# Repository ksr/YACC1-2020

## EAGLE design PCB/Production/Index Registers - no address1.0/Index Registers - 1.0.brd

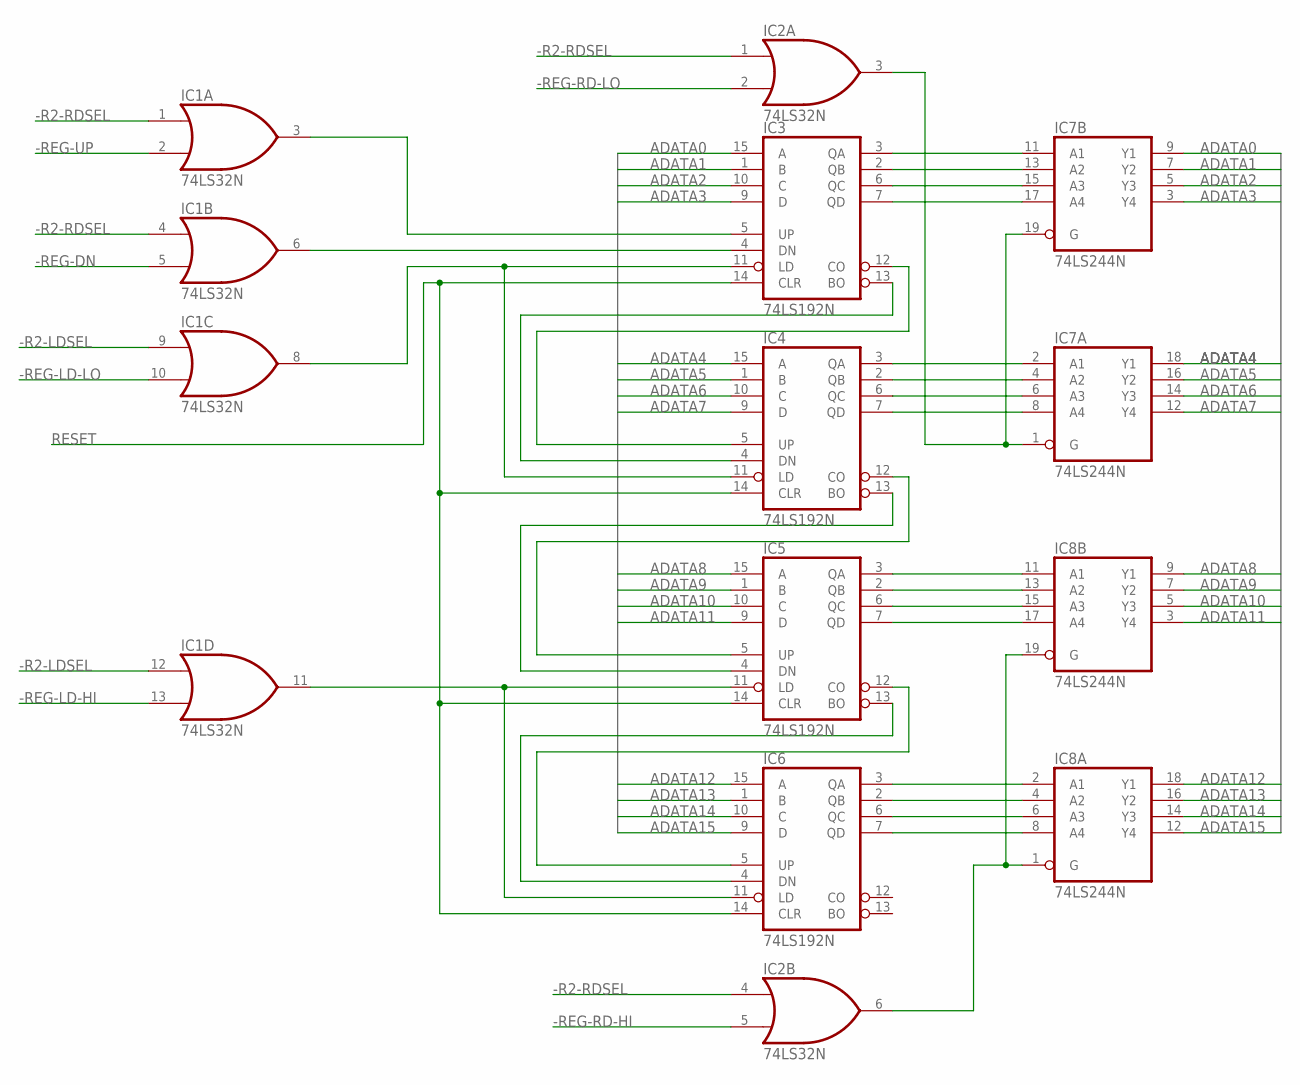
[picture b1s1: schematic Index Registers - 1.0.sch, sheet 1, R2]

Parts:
IC1, IC2: 74LS32N; DIL14
IC3, IC4, IC5, IC6: 74LS192N; DIL16
IC7, IC8: 74LS244N; DIL20

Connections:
-R2-LDSEL: IC1.9 (I0), IC1.12 (I0); also elsewhere on the board
-R2-RDSEL: IC1.1 (I0), IC1.4 (I0), IC2.1 (I0), IC2.4 (I0); also elsewhere on the board
-REG-DN: IC1.5 (I1); also elsewhere on the board
-REG-LD-HI: IC1.13 (I1); also elsewhere on the board
-REG-LD-LO: IC1.10 (I1); also elsewhere on the board
-REG-RD-HI: IC2.5 (I1); also elsewhere on the board
-REG-RD-LO: IC2.2 (I1); also elsewhere on the board
-REG-UP: IC1.2 (I1); also elsewhere on the board
ADATA0: IC3.15 (A), IC7.9 (Y1); also elsewhere on the board
ADATA1: IC3.1 (B), IC7.7 (Y2); also elsewhere on the board
ADATA2: IC3.10 (C), IC7.5 (Y3); also elsewhere on the board
ADATA3: IC3.9 (D), IC7.3 (Y4); also elsewhere on the board
ADATA4: IC4.15 (A), IC7.18 (Y1); also elsewhere on the board
ADATA5: IC4.1 (B), IC7.16 (Y2); also elsewhere on the board
ADATA6: IC4.10 (C), IC7.14 (Y3); also elsewhere on the board
ADATA7: IC4.9 (D), IC7.12 (Y4); also elsewhere on the board
ADATA8: IC5.15 (A), IC8.9 (Y1); also elsewhere on the board
ADATA9: IC5.1 (B), IC8.7 (Y2); also elsewhere on the board
ADATA10: IC5.10 (C), IC8.5 (Y3); also elsewhere on the board
ADATA11: IC5.9 (D), IC8.3 (Y4); also elsewhere on the board
ADATA12: IC6.15 (A), IC8.18 (Y1); also elsewhere on the board
ADATA13: IC6.1 (B), IC8.16 (Y2); also elsewhere on the board
ADATA14: IC6.10 (C), IC8.14 (Y3); also elsewhere on the board
ADATA15: IC6.9 (D), IC8.12 (Y4); also elsewhere on the board
GND: IC1.7 (GND), IC2.7 (GND), IC3.8 (GND), IC4.8 (GND), IC5.8 (GND), IC6.8 (GND), IC7.10 (GND), IC8.10 (GND); also elsewhere on the board
unnamed: IC3.13 (BO), IC4.4 (DN)
unnamed: IC3.12 (CO), IC4.5 (UP)
unnamed: IC4.13 (BO), IC5.4 (DN)
unnamed: IC4.12 (CO), IC5.5 (UP)
unnamed: IC5.13 (BO), IC6.4 (DN)
unnamed: IC5.12 (CO), IC6.5 (UP)
unnamed: IC1.8 (O), IC3.11 (LD), IC4.11 (LD)
unnamed: IC1.3 (O), IC3.5 (UP)
unnamed: IC1.6 (O), IC3.4 (DN)
unnamed: IC2.3 (O), IC7.1 (G), IC7.19 (G)
unnamed: IC2.6 (O), IC8.1 (G), IC8.19 (G)
unnamed: IC1.11 (O), IC5.11 (LD), IC6.11 (LD)
unnamed: IC3.3 (QA), IC7.11 (A1)
unnamed: IC3.2 (QB), IC7.13 (A2)
unnamed: IC3.6 (QC), IC7.15 (A3)
unnamed: IC3.7 (QD), IC7.17 (A4)
unnamed: IC4.3 (QA), IC7.2 (A1)
unnamed: IC4.2 (QB), IC7.4 (A2)
unnamed: IC4.6 (QC), IC7.6 (A3)
unnamed: IC4.7 (QD), IC7.8 (A4)
unnamed: IC5.3 (QA), IC8.11 (A1)
unnamed: IC5.2 (QB), IC8.13 (A2)
unnamed: IC5.6 (QC), IC8.15 (A3)
unnamed: IC5.7 (QD), IC8.17 (A4)
unnamed: IC6.3 (QA), IC8.2 (A1)
unnamed: IC6.2 (QB), IC8.4 (A2)
unnamed: IC6.6 (QC), IC8.6 (A3)
unnamed: IC6.7 (QD), IC8.8 (A4)
RESET: IC3.14 (CLR), IC4.14 (CLR), IC5.14 (CLR), IC6.14 (CLR); also elsewhere on the board
VCC: IC1.14 (VCC), IC2.14 (VCC), IC3.16 (VCC), IC4.16 (VCC), IC5.16 (VCC), IC6.16 (VCC), IC7.20 (VCC), IC8.20 (VCC); also elsewhere on the board

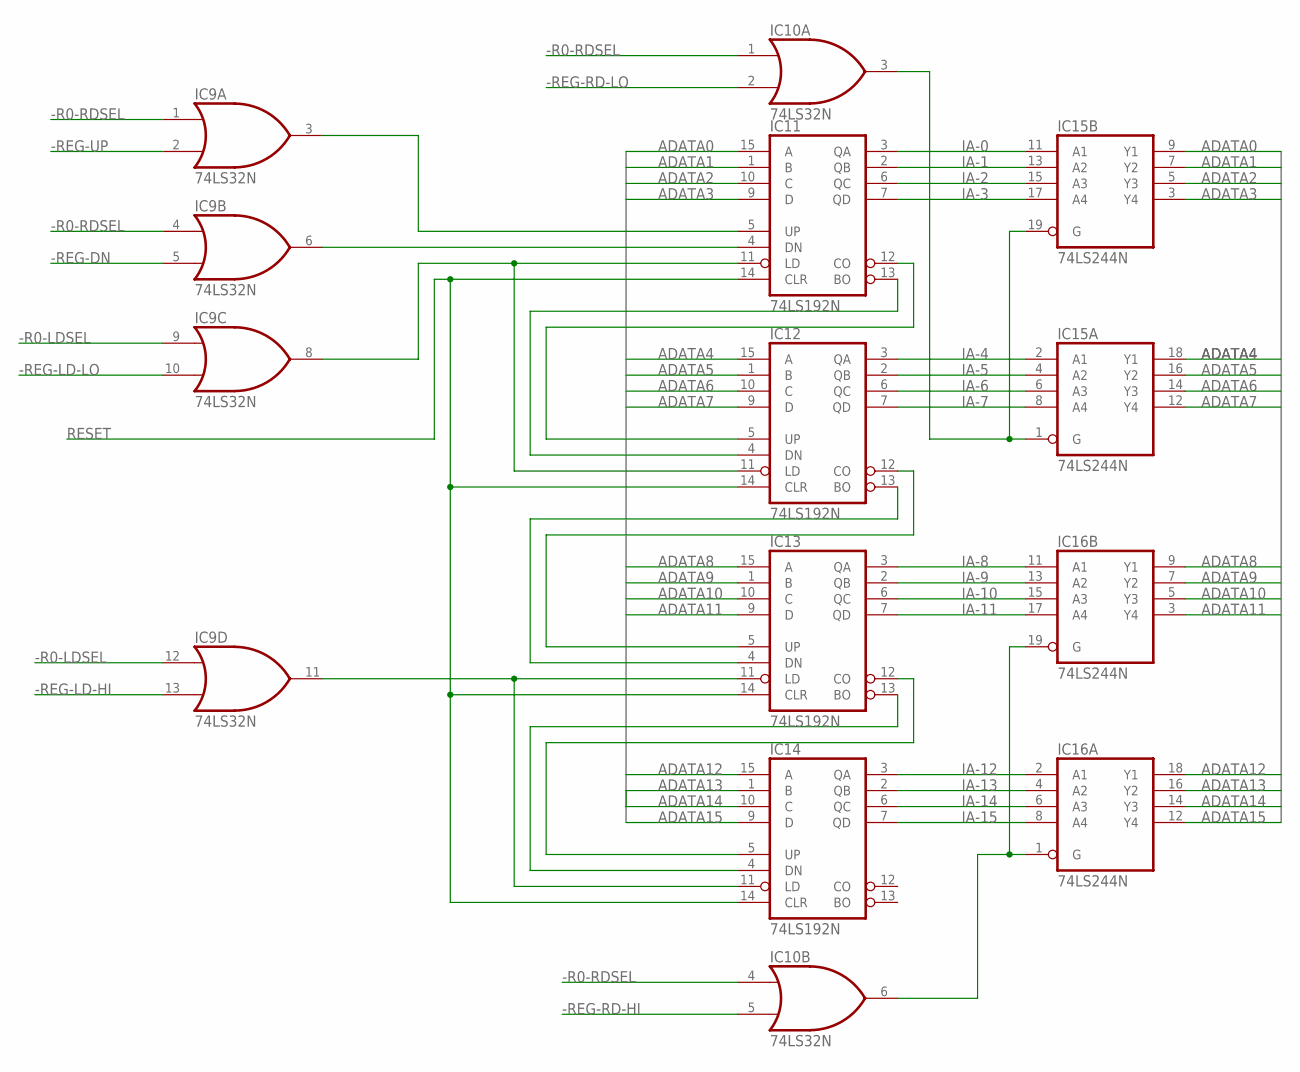
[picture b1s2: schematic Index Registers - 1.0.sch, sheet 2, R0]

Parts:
IC9, IC10: 74LS32N; DIL14
IC11, IC12, IC13, IC14: 74LS192N; DIL16
IC15, IC16: 74LS244N; DIL20

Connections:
-R0-LDSEL: IC9.9 (I0), IC9.12 (I0); also elsewhere on the board
-R0-RDSEL: IC9.1 (I0), IC9.4 (I0), IC10.1 (I0), IC10.4 (I0); also elsewhere on the board
-REG-DN: IC9.5 (I1); also elsewhere on the board
-REG-LD-HI: IC9.13 (I1); also elsewhere on the board
-REG-LD-LO: IC9.10 (I1); also elsewhere on the board
-REG-RD-HI: IC10.5 (I1); also elsewhere on the board
-REG-RD-LO: IC10.2 (I1); also elsewhere on the board
-REG-UP: IC9.2 (I1); also elsewhere on the board
ADATA0: IC11.15 (A), IC15.9 (Y1); also elsewhere on the board
ADATA1: IC11.1 (B), IC15.7 (Y2); also elsewhere on the board
ADATA2: IC11.10 (C), IC15.5 (Y3); also elsewhere on the board
ADATA3: IC11.9 (D), IC15.3 (Y4); also elsewhere on the board
ADATA4: IC12.15 (A), IC15.18 (Y1); also elsewhere on the board
ADATA5: IC12.1 (B), IC15.16 (Y2); also elsewhere on the board
ADATA6: IC12.10 (C), IC15.14 (Y3); also elsewhere on the board
ADATA7: IC12.9 (D), IC15.12 (Y4); also elsewhere on the board
ADATA8: IC13.15 (A), IC16.9 (Y1); also elsewhere on the board
ADATA9: IC13.1 (B), IC16.7 (Y2); also elsewhere on the board
ADATA10: IC13.10 (C), IC16.5 (Y3); also elsewhere on the board
ADATA11: IC13.9 (D), IC16.3 (Y4); also elsewhere on the board
ADATA12: IC14.15 (A), IC16.18 (Y1); also elsewhere on the board
ADATA13: IC14.1 (B), IC16.16 (Y2); also elsewhere on the board
ADATA14: IC14.10 (C), IC16.14 (Y3); also elsewhere on the board
ADATA15: IC14.9 (D), IC16.12 (Y4); also elsewhere on the board
GND: IC9.7 (GND), IC10.7 (GND), IC11.8 (GND), IC12.8 (GND), IC13.8 (GND), IC14.8 (GND), IC15.10 (GND), IC16.10 (GND); also elsewhere on the board
IA-0: IC11.3 (QA), IC15.11 (A1); also elsewhere on the board
IA-1: IC11.2 (QB), IC15.13 (A2); also elsewhere on the board
IA-2: IC11.6 (QC), IC15.15 (A3); also elsewhere on the board
IA-3: IC11.7 (QD), IC15.17 (A4); also elsewhere on the board
IA-4: IC12.3 (QA), IC15.2 (A1); also elsewhere on the board
IA-5: IC12.2 (QB), IC15.4 (A2); also elsewhere on the board
IA-6: IC12.6 (QC), IC15.6 (A3); also elsewhere on the board
IA-7: IC12.7 (QD), IC15.8 (A4); also elsewhere on the board
IA-8: IC13.3 (QA), IC16.11 (A1); also elsewhere on the board
IA-9: IC13.2 (QB), IC16.13 (A2); also elsewhere on the board
IA-10: IC13.6 (QC), IC16.15 (A3); also elsewhere on the board
IA-11: IC13.7 (QD), IC16.17 (A4); also elsewhere on the board
IA-12: IC14.3 (QA), IC16.2 (A1); also elsewhere on the board
IA-13: IC14.2 (QB), IC16.4 (A2); also elsewhere on the board
IA-14: IC14.6 (QC), IC16.6 (A3); also elsewhere on the board
IA-15: IC14.7 (QD), IC16.8 (A4); also elsewhere on the board
unnamed: IC11.13 (BO), IC12.4 (DN)
unnamed: IC11.12 (CO), IC12.5 (UP)
unnamed: IC12.13 (BO), IC13.4 (DN)
unnamed: IC12.12 (CO), IC13.5 (UP)
unnamed: IC13.13 (BO), IC14.4 (DN)
unnamed: IC13.12 (CO), IC14.5 (UP)
unnamed: IC9.8 (O), IC11.11 (LD), IC12.11 (LD)
unnamed: IC9.3 (O), IC11.5 (UP)
unnamed: IC9.6 (O), IC11.4 (DN)
unnamed: IC10.3 (O), IC15.1 (G), IC15.19 (G)
unnamed: IC10.6 (O), IC16.1 (G), IC16.19 (G)
unnamed: IC9.11 (O), IC13.11 (LD), IC14.11 (LD)
RESET: IC11.14 (CLR), IC12.14 (CLR), IC13.14 (CLR), IC14.14 (CLR); also elsewhere on the board
VCC: IC9.14 (VCC), IC10.14 (VCC), IC11.16 (VCC), IC12.16 (VCC), IC13.16 (VCC), IC14.16 (VCC), IC15.20 (VCC), IC16.20 (VCC); also elsewhere on the board

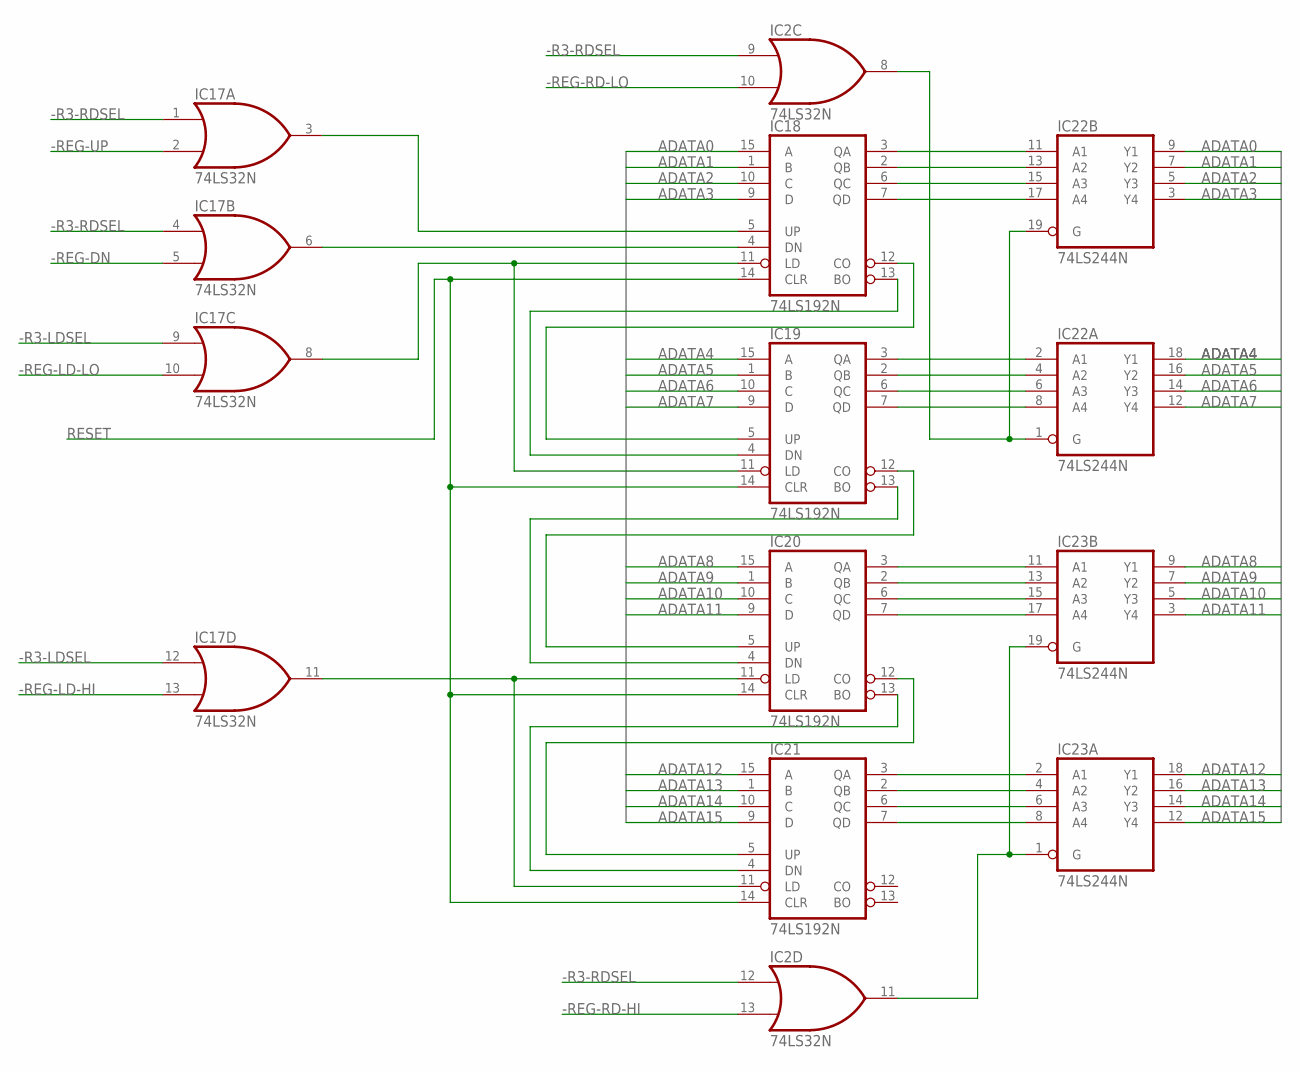
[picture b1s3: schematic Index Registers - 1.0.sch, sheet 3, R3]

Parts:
IC2, IC17: 74LS32N; DIL14
IC18, IC19, IC20, IC21: 74LS192N; DIL16
IC22, IC23: 74LS244N; DIL20

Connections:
-R3-LDSEL: IC17.9 (I0), IC17.12 (I0); also elsewhere on the board
-R3-RDSEL: IC2.9 (I0), IC2.12 (I0), IC17.1 (I0), IC17.4 (I0); also elsewhere on the board
-REG-DN: IC17.5 (I1); also elsewhere on the board
-REG-LD-HI: IC17.13 (I1); also elsewhere on the board
-REG-LD-LO: IC17.10 (I1); also elsewhere on the board
-REG-RD-HI: IC2.13 (I1); also elsewhere on the board
-REG-RD-LO: IC2.10 (I1); also elsewhere on the board
-REG-UP: IC17.2 (I1); also elsewhere on the board
ADATA0: IC18.15 (A), IC22.9 (Y1); also elsewhere on the board
ADATA1: IC18.1 (B), IC22.7 (Y2); also elsewhere on the board
ADATA2: IC18.10 (C), IC22.5 (Y3); also elsewhere on the board
ADATA3: IC18.9 (D), IC22.3 (Y4); also elsewhere on the board
ADATA4: IC19.15 (A), IC22.18 (Y1); also elsewhere on the board
ADATA5: IC19.1 (B), IC22.16 (Y2); also elsewhere on the board
ADATA6: IC19.10 (C), IC22.14 (Y3); also elsewhere on the board
ADATA7: IC19.9 (D), IC22.12 (Y4); also elsewhere on the board
ADATA8: IC20.15 (A), IC23.9 (Y1); also elsewhere on the board
ADATA9: IC20.1 (B), IC23.7 (Y2); also elsewhere on the board
ADATA10: IC20.10 (C), IC23.5 (Y3); also elsewhere on the board
ADATA11: IC20.9 (D), IC23.3 (Y4); also elsewhere on the board
ADATA12: IC21.15 (A), IC23.18 (Y1); also elsewhere on the board
ADATA13: IC21.1 (B), IC23.16 (Y2); also elsewhere on the board
ADATA14: IC21.10 (C), IC23.14 (Y3); also elsewhere on the board
ADATA15: IC21.9 (D), IC23.12 (Y4); also elsewhere on the board
GND: IC2.7 (GND), IC17.7 (GND), IC18.8 (GND), IC19.8 (GND), IC20.8 (GND), IC21.8 (GND), IC22.10 (GND), IC23.10 (GND); also elsewhere on the board
unnamed: IC18.13 (BO), IC19.4 (DN)
unnamed: IC18.12 (CO), IC19.5 (UP)
unnamed: IC19.13 (BO), IC20.4 (DN)
unnamed: IC19.12 (CO), IC20.5 (UP)
unnamed: IC20.13 (BO), IC21.4 (DN)
unnamed: IC20.12 (CO), IC21.5 (UP)
unnamed: IC17.8 (O), IC18.11 (LD), IC19.11 (LD)
unnamed: IC17.3 (O), IC18.5 (UP)
unnamed: IC17.6 (O), IC18.4 (DN)
unnamed: IC18.3 (QA), IC22.11 (A1)
unnamed: IC18.2 (QB), IC22.13 (A2)
unnamed: IC18.6 (QC), IC22.15 (A3)
unnamed: IC18.7 (QD), IC22.17 (A4)
unnamed: IC2.8 (O), IC22.1 (G), IC22.19 (G)
unnamed: IC2.11 (O), IC23.1 (G), IC23.19 (G)
unnamed: IC17.11 (O), IC20.11 (LD), IC21.11 (LD)
unnamed: IC19.3 (QA), IC22.2 (A1)
unnamed: IC19.2 (QB), IC22.4 (A2)
unnamed: IC19.6 (QC), IC22.6 (A3)
unnamed: IC19.7 (QD), IC22.8 (A4)
unnamed: IC20.3 (QA), IC23.11 (A1)
unnamed: IC20.2 (QB), IC23.13 (A2)
unnamed: IC20.6 (QC), IC23.15 (A3)
unnamed: IC20.7 (QD), IC23.17 (A4)
unnamed: IC21.3 (QA), IC23.2 (A1)
unnamed: IC21.2 (QB), IC23.4 (A2)
unnamed: IC21.6 (QC), IC23.6 (A3)
unnamed: IC21.7 (QD), IC23.8 (A4)
RESET: IC18.14 (CLR), IC19.14 (CLR), IC20.14 (CLR), IC21.14 (CLR); also elsewhere on the board
VCC: IC2.14 (VCC), IC17.14 (VCC), IC18.16 (VCC), IC19.16 (VCC), IC20.16 (VCC), IC21.16 (VCC), IC22.20 (VCC), IC23.20 (VCC); also elsewhere on the board

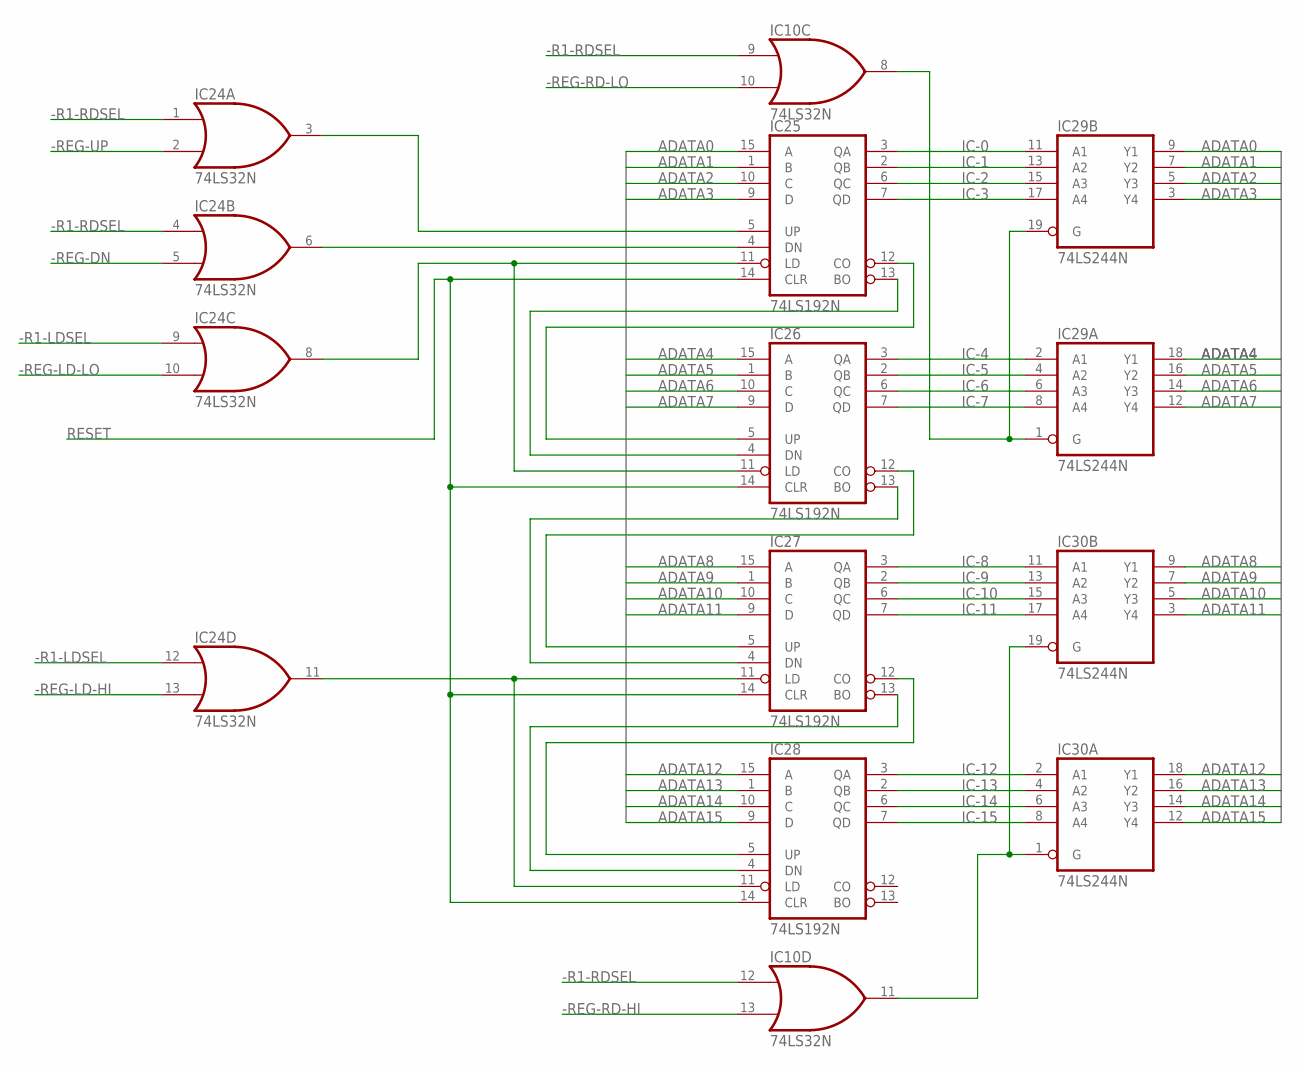
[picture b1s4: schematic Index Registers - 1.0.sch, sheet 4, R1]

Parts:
IC10, IC24: 74LS32N; DIL14
IC25, IC26, IC27, IC28: 74LS192N; DIL16
IC29, IC30: 74LS244N; DIL20

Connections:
-R1-LDSEL: IC24.9 (I0), IC24.12 (I0); also elsewhere on the board
-R1-RDSEL: IC10.9 (I0), IC10.12 (I0), IC24.1 (I0), IC24.4 (I0); also elsewhere on the board
-REG-DN: IC24.5 (I1); also elsewhere on the board
-REG-LD-HI: IC24.13 (I1); also elsewhere on the board
-REG-LD-LO: IC24.10 (I1); also elsewhere on the board
-REG-RD-HI: IC10.13 (I1); also elsewhere on the board
-REG-RD-LO: IC10.10 (I1); also elsewhere on the board
-REG-UP: IC24.2 (I1); also elsewhere on the board
ADATA0: IC25.15 (A), IC29.9 (Y1); also elsewhere on the board
ADATA1: IC25.1 (B), IC29.7 (Y2); also elsewhere on the board
ADATA2: IC25.10 (C), IC29.5 (Y3); also elsewhere on the board
ADATA3: IC25.9 (D), IC29.3 (Y4); also elsewhere on the board
ADATA4: IC26.15 (A), IC29.18 (Y1); also elsewhere on the board
ADATA5: IC26.1 (B), IC29.16 (Y2); also elsewhere on the board
ADATA6: IC26.10 (C), IC29.14 (Y3); also elsewhere on the board
ADATA7: IC26.9 (D), IC29.12 (Y4); also elsewhere on the board
ADATA8: IC27.15 (A), IC30.9 (Y1); also elsewhere on the board
ADATA9: IC27.1 (B), IC30.7 (Y2); also elsewhere on the board
ADATA10: IC27.10 (C), IC30.5 (Y3); also elsewhere on the board
ADATA11: IC27.9 (D), IC30.3 (Y4); also elsewhere on the board
ADATA12: IC28.15 (A), IC30.18 (Y1); also elsewhere on the board
ADATA13: IC28.1 (B), IC30.16 (Y2); also elsewhere on the board
ADATA14: IC28.10 (C), IC30.14 (Y3); also elsewhere on the board
ADATA15: IC28.9 (D), IC30.12 (Y4); also elsewhere on the board
GND: IC10.7 (GND), IC24.7 (GND), IC25.8 (GND), IC26.8 (GND), IC27.8 (GND), IC28.8 (GND), IC29.10 (GND), IC30.10 (GND); also elsewhere on the board
IC-0: IC25.3 (QA), IC29.11 (A1); also elsewhere on the board
IC-1: IC25.2 (QB), IC29.13 (A2); also elsewhere on the board
IC-2: IC25.6 (QC), IC29.15 (A3); also elsewhere on the board
IC-3: IC25.7 (QD), IC29.17 (A4); also elsewhere on the board
IC-4: IC26.3 (QA), IC29.2 (A1); also elsewhere on the board
IC-5: IC26.2 (QB), IC29.4 (A2); also elsewhere on the board
IC-6: IC26.6 (QC), IC29.6 (A3); also elsewhere on the board
IC-7: IC26.7 (QD), IC29.8 (A4); also elsewhere on the board
IC-8: IC27.3 (QA), IC30.11 (A1); also elsewhere on the board
IC-9: IC27.2 (QB), IC30.13 (A2); also elsewhere on the board
IC-10: IC27.6 (QC), IC30.15 (A3); also elsewhere on the board
IC-11: IC27.7 (QD), IC30.17 (A4); also elsewhere on the board
IC-12: IC28.3 (QA), IC30.2 (A1)
IC-13: IC28.2 (QB), IC30.4 (A2); also elsewhere on the board
IC-14: IC28.6 (QC), IC30.6 (A3); also elsewhere on the board
IC-15: IC28.7 (QD), IC30.8 (A4); also elsewhere on the board
unnamed: IC25.13 (BO), IC26.4 (DN)
unnamed: IC25.12 (CO), IC26.5 (UP)
unnamed: IC26.13 (BO), IC27.4 (DN)
unnamed: IC26.12 (CO), IC27.5 (UP)
unnamed: IC27.13 (BO), IC28.4 (DN)
unnamed: IC27.12 (CO), IC28.5 (UP)
unnamed: IC24.8 (O), IC25.11 (LD), IC26.11 (LD)
unnamed: IC24.3 (O), IC25.5 (UP)
unnamed: IC24.6 (O), IC25.4 (DN)
unnamed: IC10.8 (O), IC29.1 (G), IC29.19 (G)
unnamed: IC10.11 (O), IC30.1 (G), IC30.19 (G)
unnamed: IC24.11 (O), IC27.11 (LD), IC28.11 (LD)
RESET: IC25.14 (CLR), IC26.14 (CLR), IC27.14 (CLR), IC28.14 (CLR); also elsewhere on the board
VCC: IC10.14 (VCC), IC24.14 (VCC), IC25.16 (VCC), IC26.16 (VCC), IC27.16 (VCC), IC28.16 (VCC), IC29.20 (VCC), IC30.20 (VCC); also elsewhere on the board

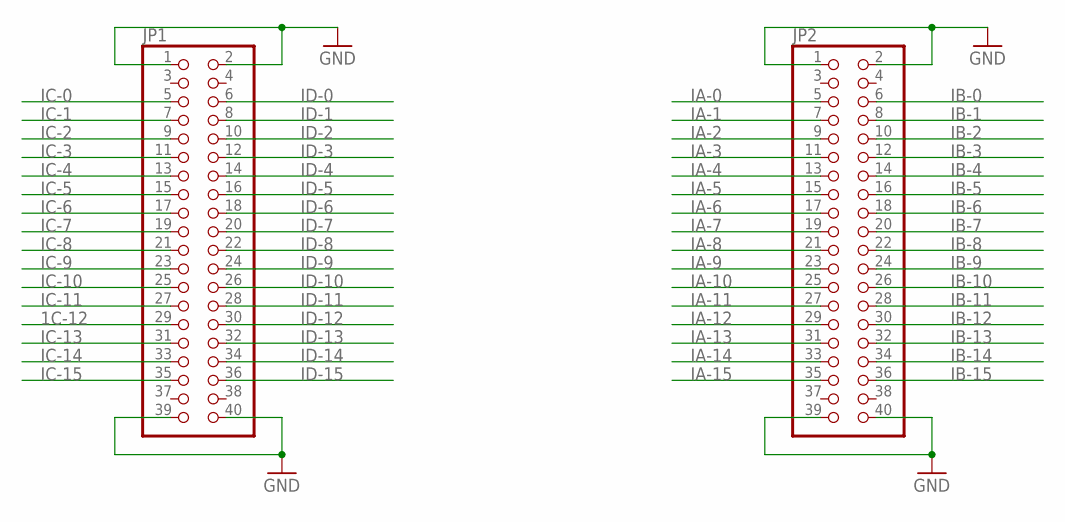
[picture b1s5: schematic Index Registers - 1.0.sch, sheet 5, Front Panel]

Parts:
JP1, JP2: PINHD-2X20; 2X20

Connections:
1C-12: JP1.29
GND: JP1.1, JP1.2, JP1.39, JP1.40, JP2.1, JP2.2, JP2.39, JP2.40; also elsewhere on the board
IA-0: JP2.5; also elsewhere on the board
IA-1: JP2.7; also elsewhere on the board
IA-2: JP2.9; also elsewhere on the board
IA-3: JP2.11; also elsewhere on the board
IA-4: JP2.13; also elsewhere on the board
IA-5: JP2.15; also elsewhere on the board
IA-6: JP2.17; also elsewhere on the board
IA-7: JP2.19; also elsewhere on the board
IA-8: JP2.21; also elsewhere on the board
IA-9: JP2.23; also elsewhere on the board
IA-10: JP2.25; also elsewhere on the board
IA-11: JP2.27; also elsewhere on the board
IA-12: JP2.29; also elsewhere on the board
IA-13: JP2.31; also elsewhere on the board
IA-14: JP2.33; also elsewhere on the board
IA-15: JP2.35; also elsewhere on the board
IB-0: JP2.6
IB-1: JP2.8
IB-2: JP2.10
IB-3: JP2.12
IB-4: JP2.14
IB-5: JP2.16
IB-6: JP2.18
IB-7: JP2.20
IB-8: JP2.22
IB-9: JP2.24
IB-10: JP2.26
IB-11: JP2.28
IB-12: JP2.30
IB-13: JP2.32
IB-14: JP2.34
IB-15: JP2.36
IC-0: JP1.5; also elsewhere on the board
IC-1: JP1.7; also elsewhere on the board
IC-2: JP1.9; also elsewhere on the board
IC-3: JP1.11; also elsewhere on the board
IC-4: JP1.13; also elsewhere on the board
IC-5: JP1.15; also elsewhere on the board
IC-6: JP1.17; also elsewhere on the board
IC-7: JP1.19; also elsewhere on the board
IC-8: JP1.21; also elsewhere on the board
IC-9: JP1.23; also elsewhere on the board
IC-10: JP1.25; also elsewhere on the board
IC-11: JP1.27; also elsewhere on the board
IC-13: JP1.31; also elsewhere on the board
IC-14: JP1.33; also elsewhere on the board
IC-15: JP1.35; also elsewhere on the board
ID-0: JP1.6
ID-1: JP1.8
ID-2: JP1.10
ID-3: JP1.12
ID-4: JP1.14
ID-5: JP1.16
ID-6: JP1.18
ID-7: JP1.20
ID-8: JP1.22
ID-9: JP1.24
ID-10: JP1.26
ID-11: JP1.28
ID-12: JP1.30
ID-13: JP1.32
ID-14: JP1.34
ID-15: JP1.36

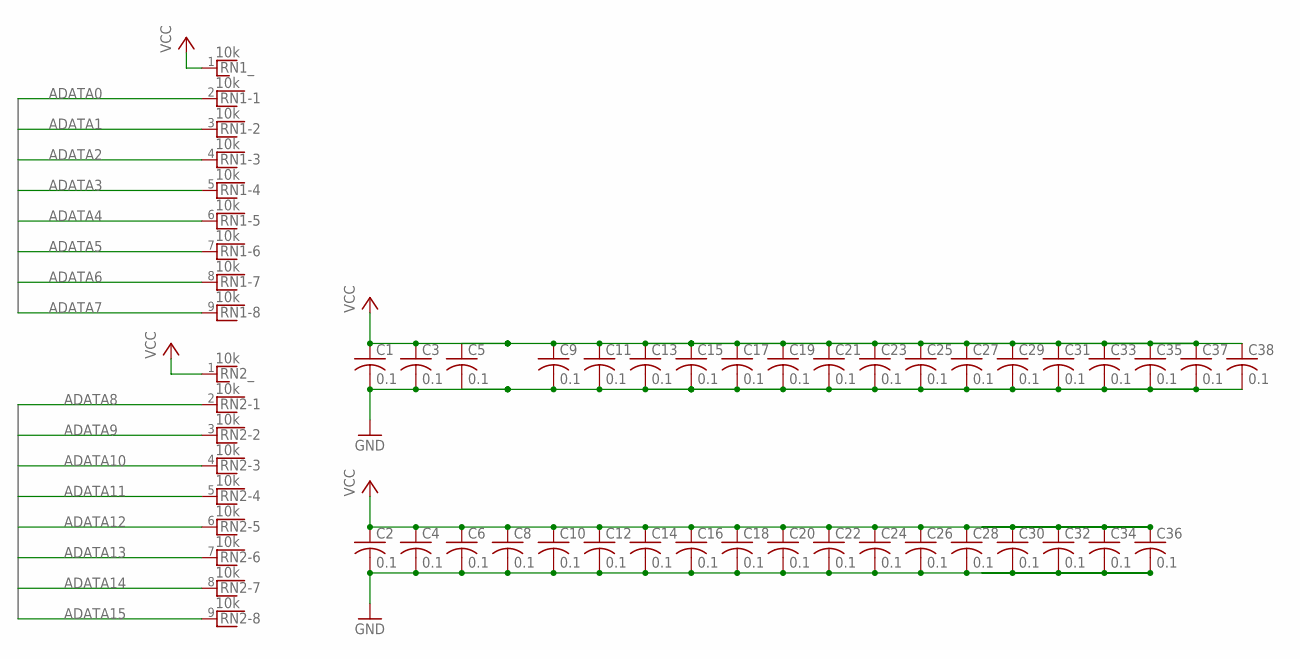
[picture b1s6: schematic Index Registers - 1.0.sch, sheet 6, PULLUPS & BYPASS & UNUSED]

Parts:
C1, C2, C3, C4, C5, C6, C8, C9, C10, C11, C12, C13, C14, C15, C16, C17, C18, C19, C20, C21, C22, C23, C24, C25, C26, C27, C28, C29, C30, C31, C32, C33, C34, C35, C36, C37, C38: 0.1; C025-040X050
RN1, RN2: 10k; RN-9

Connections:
ADATA0: RN1.2; also elsewhere on the board
ADATA1: RN1.3; also elsewhere on the board
ADATA2: RN1.4; also elsewhere on the board
ADATA3: RN1.5; also elsewhere on the board
ADATA4: RN1.6; also elsewhere on the board
ADATA5: RN1.7; also elsewhere on the board
ADATA6: RN1.8; also elsewhere on the board
ADATA7: RN1.9; also elsewhere on the board
ADATA8: RN2.2; also elsewhere on the board
ADATA9: RN2.3; also elsewhere on the board
ADATA10: RN2.4; also elsewhere on the board
ADATA11: RN2.5; also elsewhere on the board
ADATA12: RN2.6; also elsewhere on the board
ADATA13: RN2.7; also elsewhere on the board
ADATA14: RN2.8; also elsewhere on the board
ADATA15: RN2.9; also elsewhere on the board
GND: C1.2, C2.2, C3.2, C4.2, C5.2, C6.2, C8.2, C9.2, C10.2, C11.2, C12.2, C13.2, C14.2, C15.2, C16.2, C17.2, C18.2, C19.2, C20.2, C21.2, C22.2, C23.2, C24.2, C25.2, C26.2, C27.2, C28.2, C29.2, C30.2, C31.2, C32.2, C33.2, C34.2, C35.2, C36.2, C37.2, C38.2; also elsewhere on the board
VCC: C1.1, C2.1, C3.1, C4.1, C5.1, C6.1, C8.1, C9.1, C10.1, C11.1, C12.1, C13.1, C14.1, C15.1, C16.1, C17.1, C18.1, C19.1, C20.1, C21.1, C22.1, C23.1, C24.1, C25.1, C26.1, C27.1, C28.1, C29.1, C30.1, C31.1, C32.1, C33.1, C34.1, C35.1, C36.1, C37.1, C38.1, RN1.1, RN2.1; also elsewhere on the board

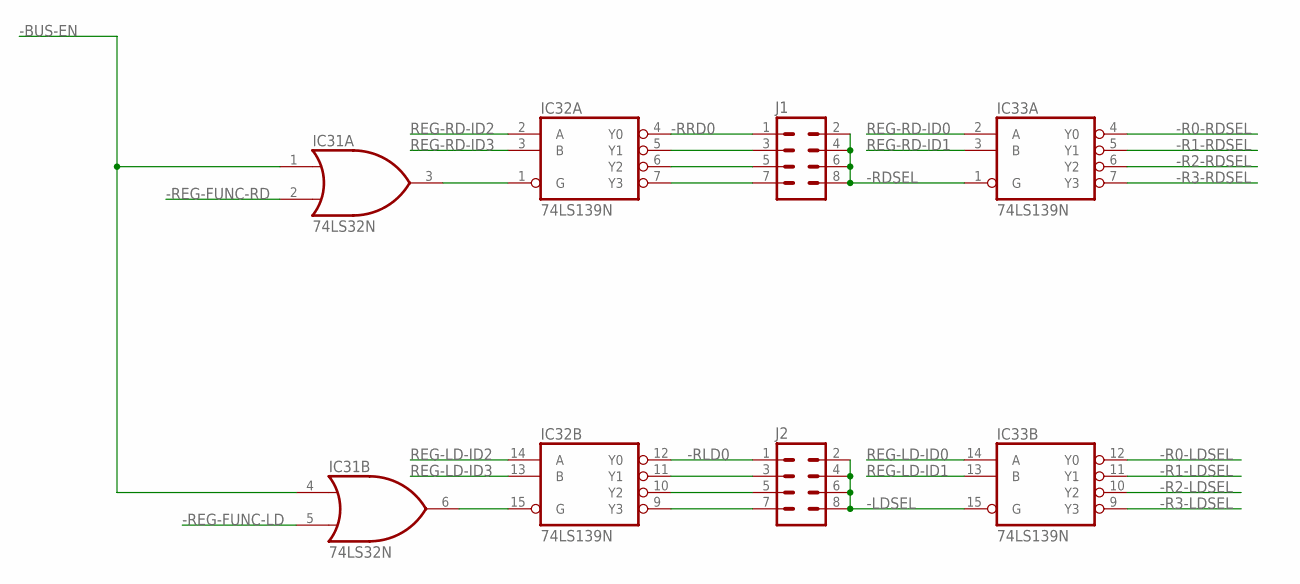
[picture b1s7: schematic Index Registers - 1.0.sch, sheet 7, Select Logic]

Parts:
IC31: 74LS32N; DIL14
IC32, IC33: 74LS139N; DIL16
J1, J2: M04X2; 2X4

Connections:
-BUS-EN: IC31.1 (I0), IC31.4 (I0); also elsewhere on the board
-LDSEL: IC33.15 (G), J2.2, J2.4, J2.6, J2.8; also elsewhere on the board
-R0-LDSEL: IC33.12 (Y0); also elsewhere on the board
-R0-RDSEL: IC33.4 (Y0); also elsewhere on the board
-R1-LDSEL: IC33.11 (Y1); also elsewhere on the board
-R1-RDSEL: IC33.5 (Y1); also elsewhere on the board
-R2-LDSEL: IC33.10 (Y2); also elsewhere on the board
-R2-RDSEL: IC33.6 (Y2); also elsewhere on the board
-R3-LDSEL: IC33.9 (Y3); also elsewhere on the board
-R3-RDSEL: IC33.7 (Y3); also elsewhere on the board
-RDSEL: IC33.1 (G), J1.2, J1.4, J1.6, J1.8; also elsewhere on the board
-REG-FUNC-LD: IC31.5 (I1); also elsewhere on the board
-REG-FUNC-RD: IC31.2 (I1); also elsewhere on the board
-RLD0: IC32.12 (Y0), J2.1
-RRD0: IC32.4 (Y0), J1.1
GND: IC31.7 (GND), IC32.8 (GND), IC33.8 (GND); also elsewhere on the board
unnamed: IC31.3 (O), IC32.1 (G)
unnamed: IC31.6 (O), IC32.15 (G)
unnamed: IC32.5 (Y1), J1.3
unnamed: IC32.6 (Y2), J1.5
unnamed: IC32.7 (Y3), J1.7
unnamed: IC32.11 (Y1), J2.3
unnamed: IC32.10 (Y2), J2.5
unnamed: IC32.9 (Y3), J2.7
REG-LD-ID0: IC33.14 (A); also elsewhere on the board
REG-LD-ID1: IC33.13 (B); also elsewhere on the board
REG-LD-ID2: IC32.14 (A); also elsewhere on the board
REG-LD-ID3: IC32.13 (B); also elsewhere on the board
REG-RD-ID0: IC33.2 (A); also elsewhere on the board
REG-RD-ID1: IC33.3 (B); also elsewhere on the board
REG-RD-ID2: IC32.2 (A); also elsewhere on the board
REG-RD-ID3: IC32.3 (B); also elsewhere on the board
VCC: IC31.14 (VCC), IC32.16 (VCC), IC33.16 (VCC); also elsewhere on the board

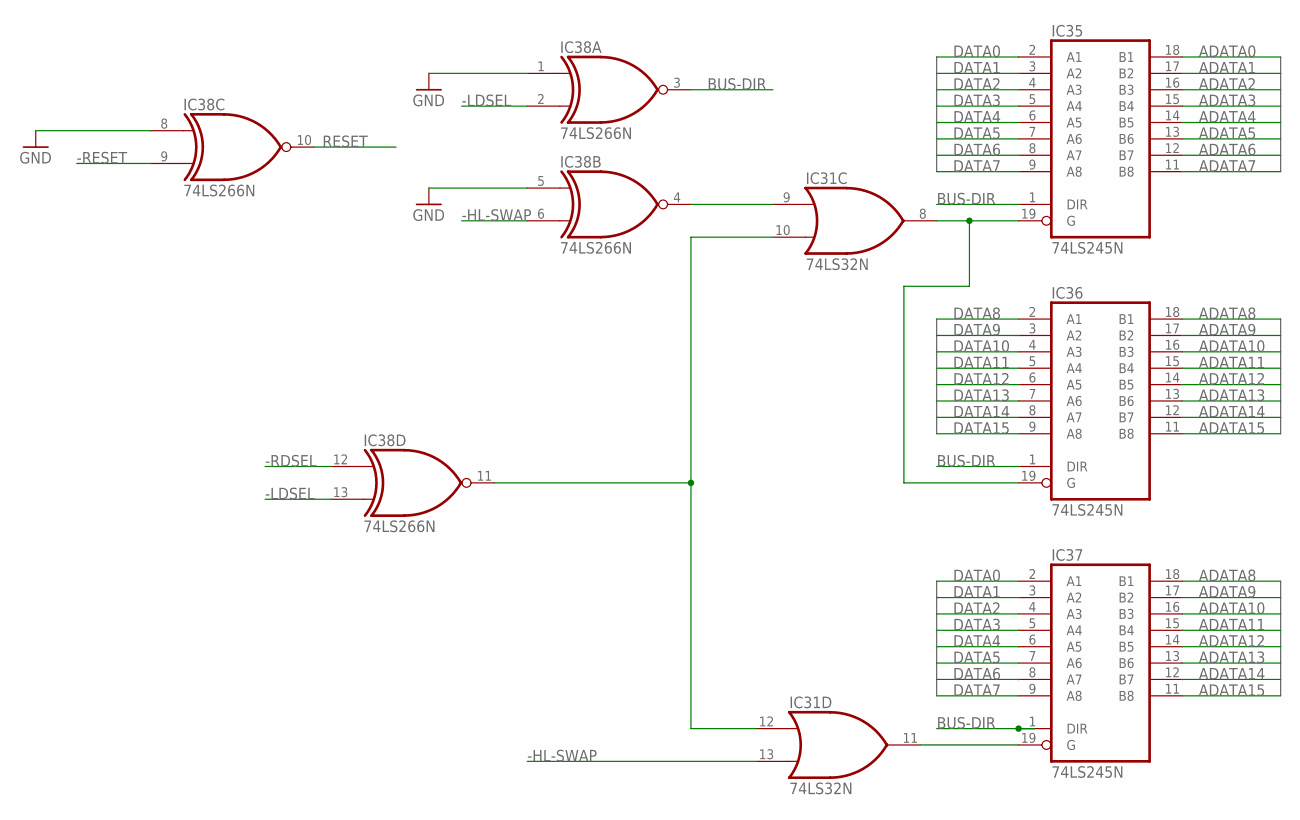
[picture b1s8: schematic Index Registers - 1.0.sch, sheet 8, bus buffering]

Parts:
IC31: 74LS32N; DIL14
IC35, IC36, IC37: 74LS245N; DIL20
IC38: 74LS266N; DIL14

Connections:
-HL-SWAP: IC31.13 (I1), IC38.6 (I1); also elsewhere on the board
-LDSEL: IC38.2 (I1), IC38.13 (I1); also elsewhere on the board
-RDSEL: IC38.12 (I0); also elsewhere on the board
-RESET: IC38.9 (I1); also elsewhere on the board
ADATA0: IC35.18 (B1); also elsewhere on the board
ADATA1: IC35.17 (B2); also elsewhere on the board
ADATA2: IC35.16 (B3); also elsewhere on the board
ADATA3: IC35.15 (B4); also elsewhere on the board
ADATA4: IC35.14 (B5); also elsewhere on the board
ADATA5: IC35.13 (B6); also elsewhere on the board
ADATA6: IC35.12 (B7); also elsewhere on the board
ADATA7: IC35.11 (B8); also elsewhere on the board
ADATA8: IC36.18 (B1), IC37.18 (B1); also elsewhere on the board
ADATA9: IC36.17 (B2), IC37.17 (B2); also elsewhere on the board
ADATA10: IC36.16 (B3), IC37.16 (B3); also elsewhere on the board
ADATA11: IC36.15 (B4), IC37.15 (B4); also elsewhere on the board
ADATA12: IC36.14 (B5), IC37.14 (B5); also elsewhere on the board
ADATA13: IC36.13 (B6), IC37.13 (B6); also elsewhere on the board
ADATA14: IC36.12 (B7), IC37.12 (B7); also elsewhere on the board
ADATA15: IC36.11 (B8), IC37.11 (B8); also elsewhere on the board
BUS-DIR: IC35.1 (DIR), IC36.1 (DIR), IC37.1 (DIR), IC38.3 (O)
DATA0: IC35.2 (A1), IC37.2 (A1); also elsewhere on the board
DATA1: IC35.3 (A2), IC37.3 (A2); also elsewhere on the board
DATA2: IC35.4 (A3), IC37.4 (A3); also elsewhere on the board
DATA3: IC35.5 (A4), IC37.5 (A4); also elsewhere on the board
DATA4: IC35.6 (A5), IC37.6 (A5); also elsewhere on the board
DATA5: IC35.7 (A6), IC37.7 (A6); also elsewhere on the board
DATA6: IC35.8 (A7), IC37.8 (A7); also elsewhere on the board
DATA7: IC35.9 (A8), IC37.9 (A8); also elsewhere on the board
DATA8: IC36.2 (A1); also elsewhere on the board
DATA9: IC36.3 (A2); also elsewhere on the board
DATA10: IC36.4 (A3); also elsewhere on the board
DATA11: IC36.5 (A4); also elsewhere on the board
DATA12: IC36.6 (A5); also elsewhere on the board
DATA13: IC36.7 (A6); also elsewhere on the board
DATA14: IC36.8 (A7); also elsewhere on the board
DATA15: IC36.9 (A8); also elsewhere on the board
GND: IC31.7 (GND), IC35.10 (GND), IC36.10 (GND), IC37.10 (GND), IC38.1 (I0), IC38.5 (I0), IC38.7 (GND), IC38.8 (I0); also elsewhere on the board
unnamed: IC31.8 (O), IC35.19 (G), IC36.19 (G)
unnamed: IC31.11 (O), IC37.19 (G)
unnamed: IC31.9 (I0), IC38.4 (O)
unnamed: IC31.10 (I1), IC31.12 (I0), IC38.11 (O)
RESET: IC38.10 (O); also elsewhere on the board
VCC: IC31.14 (VCC), IC35.20 (VCC), IC36.20 (VCC), IC37.20 (VCC), IC38.14 (VCC); also elsewhere on the board

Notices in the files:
parts and their libraries:
SparkFun-Connectors: Licensing: Creative Commons ShareAlike 4.0 International - https://creativecommons.org/licenses/by-sa/4.0
SparkFun-Electromechanical: Licensing: CC v3.0 Share-Alike You are welcome to use this library for commercial purposes.
